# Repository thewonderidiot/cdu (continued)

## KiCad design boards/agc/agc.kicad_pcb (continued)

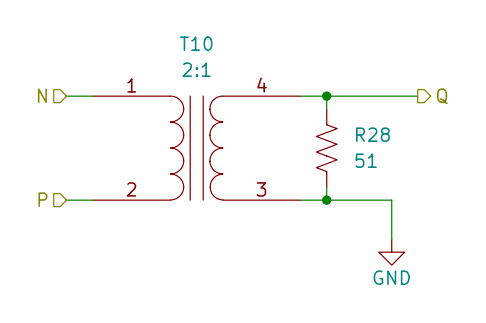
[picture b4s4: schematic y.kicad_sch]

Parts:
R28: 51; R_0603_1608Metric
T10: 2:1; Vigortronix_VTX-111

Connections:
/CDUXP: R28.1, T10.4 (SB); also elsewhere on the board
/CT+PGH: T10.1 (AA); also elsewhere on the board
/CT+PGL: T10.2 (AB); also elsewhere on the board
GND: R28.2, T10.3 (SA); also elsewhere on the board

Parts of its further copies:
R9, R10, R11, R12, R13, R24, R25, R26, R27: 51; R_0603_1608Metric
T1, T2, T3, T4, T5, T6, T7, T8, T9: 2:1; Vigortronix_VTX-111

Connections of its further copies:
/AT+PGH: T4.1 (AA); also elsewhere on the board
/AT+PGL: T4.2 (AB); also elsewhere on the board
/AT-PGH: T5.1 (AA); also elsewhere on the board
/AT-PGL: T5.2 (AB); also elsewhere on the board
/BT+PGH: T2.1 (AA); also elsewhere on the board
/BT+PGL: T2.2 (AB); also elsewhere on the board
/BT-PGH: T3.1 (AA); also elsewhere on the board
/BT-PGL: T3.2 (AB); also elsewhere on the board
/CDUXM: R9.1, T1.4 (SB); also elsewhere on the board
/CDUYM: R13.1, T5.4 (SB); also elsewhere on the board
/CDUYP: R12.1, T4.4 (SB); also elsewhere on the board
/CDUZM: R11.1, T3.4 (SB); also elsewhere on the board
/CDUZP: R10.1, T2.4 (SB); also elsewhere on the board
/CT-PGH: T1.1 (AA); also elsewhere on the board
/CT-PGL: T1.2 (AB); also elsewhere on the board
/DT+PGH: T8.1 (AA); also elsewhere on the board
/DT+PGL: T8.2 (AB); also elsewhere on the board
/DT-PGH: T9.1 (AA); also elsewhere on the board
/DT-PGL: T9.2 (AB); also elsewhere on the board
/ET+PGH: T6.1 (AA); also elsewhere on the board
/ET+PGL: T6.2 (AB); also elsewhere on the board
/ET-PGH: T7.1 (AA); also elsewhere on the board
/ET-PGL: T7.2 (AB); also elsewhere on the board
/SHAFTM: R27.1, T9.4 (SB); also elsewhere on the board
/SHAFTP: R26.1, T8.4 (SB); also elsewhere on the board
/TRNM: R25.1, T7.4 (SB); also elsewhere on the board
/TRNP: R24.1, T6.4 (SB); also elsewhere on the board
GND: R9.2, R10.2, R11.2, R12.2, R13.2, R24.2, R25.2, R26.2, R27.2, T1.3 (SA), T2.3 (SA), T3.3 (SA), T4.3 (SA), T5.3 (SA), T6.3 (SA), T7.3 (SA), T8.3 (SA), T9.3 (SA); also elsewhere on the board

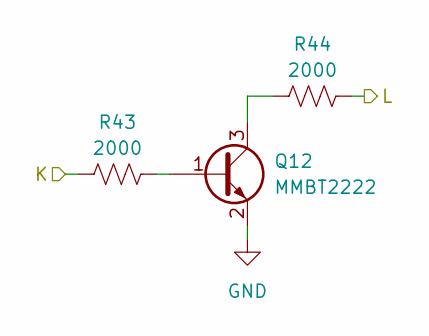
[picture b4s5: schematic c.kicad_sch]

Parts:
Q12: MMBT2222; SOT-23
R43, R44: 2000; R_0603_1608Metric

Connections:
/ISSTDC: R43.1; also elsewhere on the board
/PSATDC: R44.2; also elsewhere on the board
GND: Q12.2 (E); also elsewhere on the board
unnamed: Q12.1 (B), R43.2
unnamed: Q12.3 (C), R44.1

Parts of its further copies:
Q1, Q2, Q3, Q4, Q5, Q6, Q7: MMBT2222; SOT-23
R16, R17, R18, R19, R20, R21, R22, R23, R29, R30, R31, R32, R33, R34: 2000; R_0603_1608Metric

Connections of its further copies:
/AGCCA: R34.2; also elsewhere on the board
/AGCDAE: R21.2; also elsewhere on the board
/AGCEEC: R19.2; also elsewhere on the board
/AGCRRZ: R23.2; also elsewhere on the board
/AGCSAT: R30.2; also elsewhere on the board
/AGCTVC: R32.2; also elsewhere on the board
/AGCZ: R18.2; also elsewhere on the board
/COARSE: R33.1; also elsewhere on the board
/ENERIM: R16.1; also elsewhere on the board
/ENEROP: R20.1; also elsewhere on the board
/S4BTAK: R29.1; also elsewhere on the board
/TVCNAB: R31.1; also elsewhere on the board
/ZIMCDU: R17.1; also elsewhere on the board
/ZOPCDU: R22.1; also elsewhere on the board
GND: Q1.2 (E), Q2.2 (E), Q3.2 (E), Q4.2 (E), Q5.2 (E), Q6.2 (E), Q7.2 (E); also elsewhere on the board
unnamed: Q1.1 (B), R17.2
unnamed: Q1.3 (C), R18.1
unnamed: Q2.1 (B), R16.2
unnamed: Q2.3 (C), R19.1
unnamed: Q3.1 (B), R20.2
unnamed: Q3.3 (C), R21.1
unnamed: Q4.1 (B), R22.2
unnamed: Q4.3 (C), R23.1
unnamed: Q5.1 (B), R29.2
unnamed: Q5.3 (C), R30.1
unnamed: Q6.1 (B), R31.2
unnamed: Q6.3 (C), R32.1
unnamed: Q7.1 (B), R33.2
unnamed: Q7.3 (C), R34.1

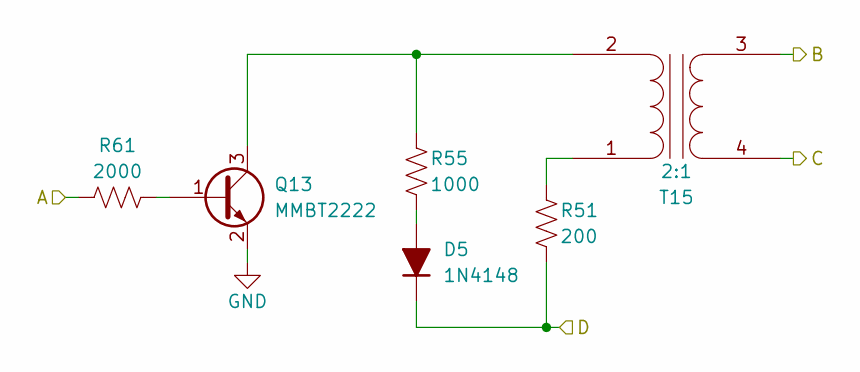
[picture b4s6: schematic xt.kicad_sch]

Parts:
D5: 1N4148; D_SOD-323
Q13: MMBT2222; SOT-23
R51: 200; R_0603_1608Metric
R55: 1000; R_0603_1608Metric
R61: 2000; R_0603_1608Metric
T15: 2:1; Vigortronix_VTX-111

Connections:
/CDUXDP: R61.1; also elsewhere on the board
/CF+PCH: T15.4 (SB); also elsewhere on the board
/CF+PCL: T15.3 (SA); also elsewhere on the board
/P1/J: D5.1 (K), R51.2; also elsewhere on the board
GND: Q13.2 (E); also elsewhere on the board
unnamed: D5.2 (A), R55.2
unnamed: Q13.1 (B), R61.2
unnamed: Q13.3 (C), R55.1, T15.2 (AB)
unnamed: R51.1, T15.1 (AA)

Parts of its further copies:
D1, D2, D3, D4, D6, D7, D8, D9, D10, D11, D12, D13, D14, D15, D16: 1N4148; D_SOD-323
Q8, Q9, Q10, Q11, Q14, Q15, Q16, Q17, Q18, Q19, Q20, Q21, Q22, Q23, Q24: MMBT2222; SOT-23
R35, R36, R37, R38, R52, R53, R54, R67, R70, R72, R74, R81, R82, R83, R84: 200; R_0603_1608Metric
R39, R40, R41, R42, R56, R57, R58, R68, R69, R71, R73, R85, R86, R87, R88: 1000; R_0603_1608Metric
R45, R46, R47, R48, R62, R63, R64, R75, R76, R77, R78, R91, R92, R93, R94: 2000; R_0603_1608Metric
T11, T12, T13, T14, T16, T17, T18, T19, T20, T21, T22, T23, T24, T25, T26: 2:1; Vigortronix_VTX-111

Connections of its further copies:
/25KPH: T22.4 (SB); also elsewhere on the board
/25KPL: T22.3 (SA); also elsewhere on the board
/25KPPS: R78.1; also elsewhere on the board
/800RH: T24.4 (SB); also elsewhere on the board
/800RL: T24.3 (SA); also elsewhere on the board
/800RST: R92.1; also elsewhere on the board
/800SET: R91.1; also elsewhere on the board
/800SH: T23.4 (SB); also elsewhere on the board
/800SL: T23.3 (SA); also elsewhere on the board
/3200A: R93.1; also elsewhere on the board
/3200AH: T25.4 (SB); also elsewhere on the board
/3200AL: T25.3 (SA); also elsewhere on the board
/3200B: R94.1; also elsewhere on the board
/3200BH: T26.4 (SB); also elsewhere on the board
/3200BL: T26.3 (SA); also elsewhere on the board
/AF+PCH: T17.4 (SB); also elsewhere on the board
/AF+PCL: T17.3 (SA); also elsewhere on the board
/AF-PCH: T18.4 (SB); also elsewhere on the board
/AF-PCL: T18.3 (SA); also elsewhere on the board
/BF+PCH: T20.4 (SB); also elsewhere on the board
/BF+PCL: T20.3 (SA); also elsewhere on the board
/BF-PCH: T21.4 (SB); also elsewhere on the board
/BF-PCL: T21.3 (SA); also elsewhere on the board
/CDUCLK: R75.1; also elsewhere on the board
/CDUXDM: R62.1; also elsewhere on the board
/CDUYDM: R64.1; also elsewhere on the board
/CDUYDP: R63.1; also elsewhere on the board
/CDUZDM: R77.1; also elsewhere on the board
/CDUZDP: R76.1; also elsewhere on the board
/CF-PCH: T16.4 (SB); also elsewhere on the board
/CF-PCL: T16.3 (SA); also elsewhere on the board
/CLOCKH: T19.4 (SB); also elsewhere on the board
/CLOCKL: T19.3 (SA); also elsewhere on the board
/DF+PCH: T13.4 (SB); also elsewhere on the board
/DF+PCL: T13.3 (SA); also elsewhere on the board
/DF-PCH: T14.4 (SB); also elsewhere on the board
/DF-PCL: T14.3 (SA); also elsewhere on the board
/EF+PCH: T11.4 (SB); also elsewhere on the board
/EF+PCL: T11.3 (SA); also elsewhere on the board
/EF-PCH: T12.4 (SB); also elsewhere on the board
/EF-PCL: T12.3 (SA); also elsewhere on the board
/P1/J: D6.1 (K), D7.1 (K), D8.1 (K), R52.2, R53.2, R54.2; also elsewhere on the board
/P2/J: D1.1 (K), D2.1 (K), D3.1 (K), D4.1 (K), R35.2, R36.2, R37.2, R38.2; also elsewhere on the board
/P3/J: D13.1 (K), D14.1 (K), D15.1 (K), D16.1 (K), R81.2, R82.2, R83.2, R84.2; also elsewhere on the board
/P4/J: D9.1 (K), D10.1 (K), D11.1 (K), D12.1 (K), R67.2, R70.2, R72.2, R74.2; also elsewhere on the board
/SHFTDM: R48.1; also elsewhere on the board
/SHFTDP: R47.1; also elsewhere on the board
/TRNDM: R46.1; also elsewhere on the board
/TRNDP: R45.1; also elsewhere on the board
GND: Q8.2 (E), Q9.2 (E), Q10.2 (E), Q11.2 (E), Q14.2 (E), Q15.2 (E), Q16.2 (E), Q17.2 (E), Q18.2 (E), Q19.2 (E), Q20.2 (E), Q21.2 (E), Q22.2 (E), Q23.2 (E), Q24.2 (E); also elsewhere on the board
unnamed: D1.2 (A), R39.2
unnamed: D2.2 (A), R40.2
unnamed: D3.2 (A), R41.2
unnamed: D4.2 (A), R42.2
unnamed: D6.2 (A), R56.2
unnamed: D7.2 (A), R57.2
unnamed: D8.2 (A), R58.2
unnamed: D9.2 (A), R68.2
unnamed: D10.2 (A), R69.2
unnamed: D11.2 (A), R71.2
unnamed: D12.2 (A), R73.2
unnamed: D13.2 (A), R85.2
unnamed: D14.2 (A), R86.2
unnamed: D15.2 (A), R87.2
unnamed: D16.2 (A), R88.2
unnamed: Q8.1 (B), R45.2
unnamed: Q8.3 (C), R39.1, T11.2 (AB)
unnamed: Q9.1 (B), R46.2
unnamed: Q9.3 (C), R40.1, T12.2 (AB)
unnamed: Q10.1 (B), R47.2
unnamed: Q10.3 (C), R41.1, T13.2 (AB)
unnamed: Q11.1 (B), R48.2
unnamed: Q11.3 (C), R42.1, T14.2 (AB)
unnamed: Q14.1 (B), R62.2
unnamed: Q14.3 (C), R56.1, T16.2 (AB)
unnamed: Q15.1 (B), R63.2
unnamed: Q15.3 (C), R57.1, T17.2 (AB)
unnamed: Q16.1 (B), R64.2
unnamed: Q16.3 (C), R58.1, T18.2 (AB)
unnamed: Q17.1 (B), R75.2
unnamed: Q17.3 (C), R68.1, T19.2 (AB)
unnamed: Q18.1 (B), R76.2
unnamed: Q18.3 (C), R69.1, T20.2 (AB)
unnamed: Q19.1 (B), R77.2
unnamed: Q19.3 (C), R71.1, T21.2 (AB)
unnamed: Q20.1 (B), R78.2
unnamed: Q20.3 (C), R73.1, T22.2 (AB)
unnamed: Q21.1 (B), R91.2
unnamed: Q21.3 (C), R85.1, T23.2 (AB)
unnamed: Q22.1 (B), R92.2
unnamed: Q22.3 (C), R86.1, T24.2 (AB)
unnamed: Q23.1 (B), R93.2
unnamed: Q23.3 (C), R87.1, T25.2 (AB)
unnamed: Q24.1 (B), R94.2
unnamed: Q24.3 (C), R88.1, T26.2 (AB)
unnamed: R35.1, T11.1 (AA)
unnamed: R36.1, T12.1 (AA)
unnamed: R37.1, T13.1 (AA)
unnamed: R38.1, T14.1 (AA)
unnamed: R52.1, T16.1 (AA)
unnamed: R53.1, T17.1 (AA)
unnamed: R54.1, T18.1 (AA)
unnamed: R67.1, T19.1 (AA)
unnamed: R70.1, T20.1 (AA)
unnamed: R72.1, T21.1 (AA)
unnamed: R74.1, T22.1 (AA)
unnamed: R81.1, T23.1 (AA)
unnamed: R82.1, T24.1 (AA)
unnamed: R83.1, T25.1 (AA)
unnamed: R84.1, T26.1 (AA)

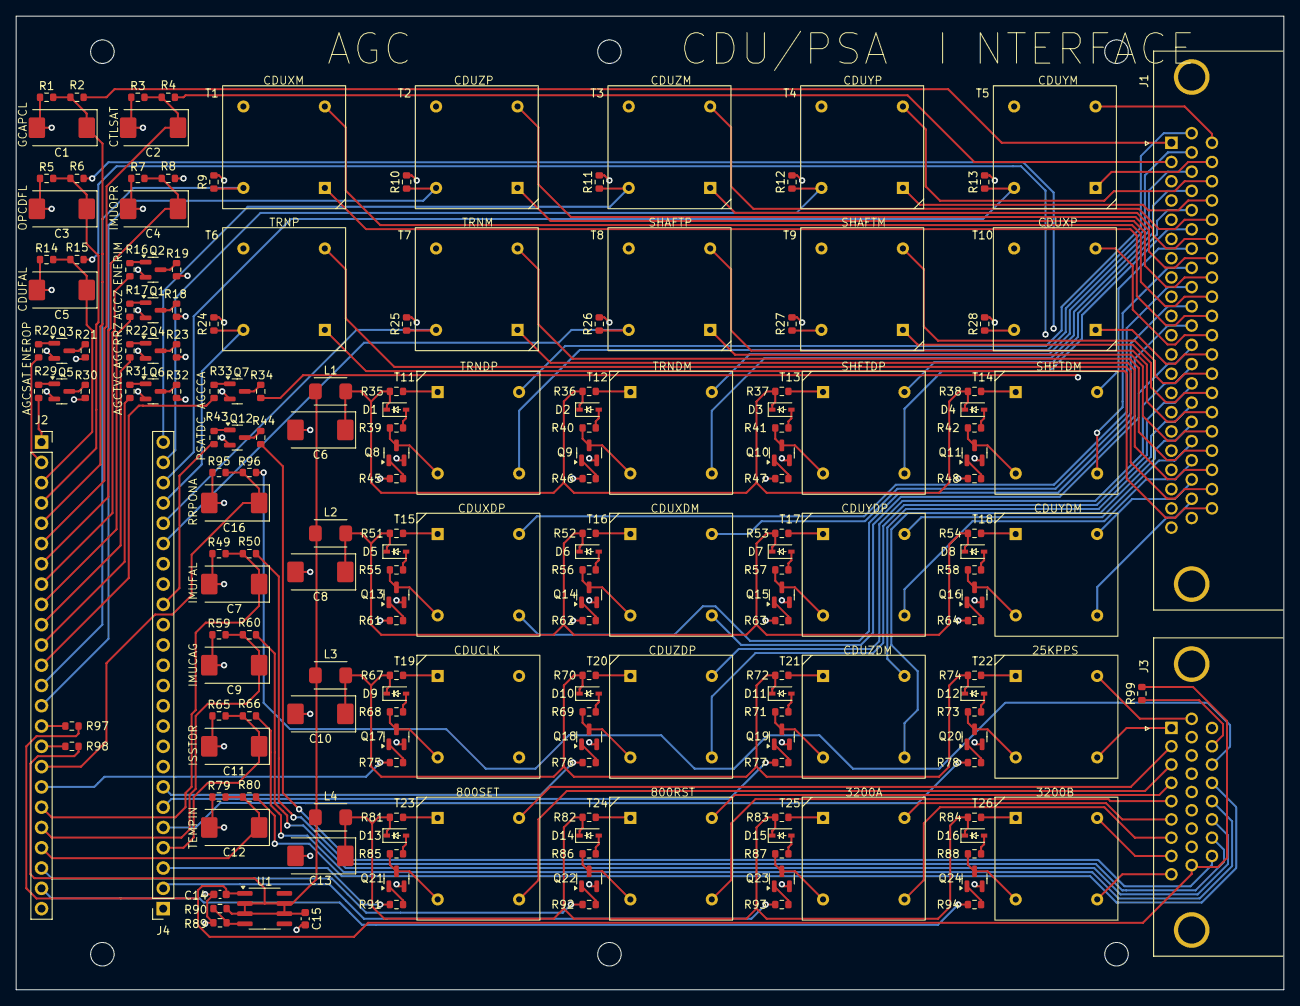
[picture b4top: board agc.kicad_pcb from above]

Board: 4 copper layers, 158.7 x 121.9 mm, 196 parts (0 on the bottom side), 205 nets.

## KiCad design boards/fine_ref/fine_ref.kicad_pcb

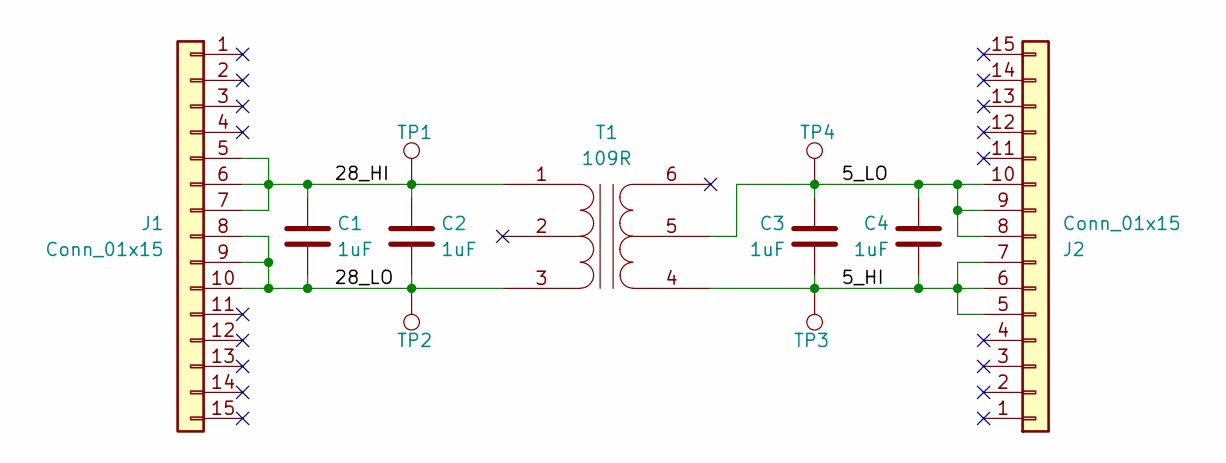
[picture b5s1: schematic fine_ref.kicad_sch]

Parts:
C1, C2, C3, C4: 1uF; C_Rect_L13.0mm_W6.0mm_P10.00mm_FKS3_FKP3_MKS4
J1, J2: Conn_01x15; PinHeader_1x15_P2.54mm_Vertical
T1: 109R; Hammond_109
TP1, TP2, TP3, TP4: TestPoint; TestPoint_Keystone_5000-5004_Miniature

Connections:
/5_HI: C3.2, C4.2, J2.5, J2.6, J2.7, T1.4 (SA), TP3.1
/5_LO: C3.1, C4.1, J2.8, J2.9, J2.10, T1.5 (SC), TP4.1
/28_HI: C1.1, C2.1, J1.5, J1.6, J1.7, T1.1 (AA), TP1.1
/28_LO: C1.2, C2.2, J1.8, J1.9, J1.10, T1.3 (AB), TP2.1

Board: 2 copper layers, 11 parts (2 on the bottom side), 4 nets, no tracks yet.

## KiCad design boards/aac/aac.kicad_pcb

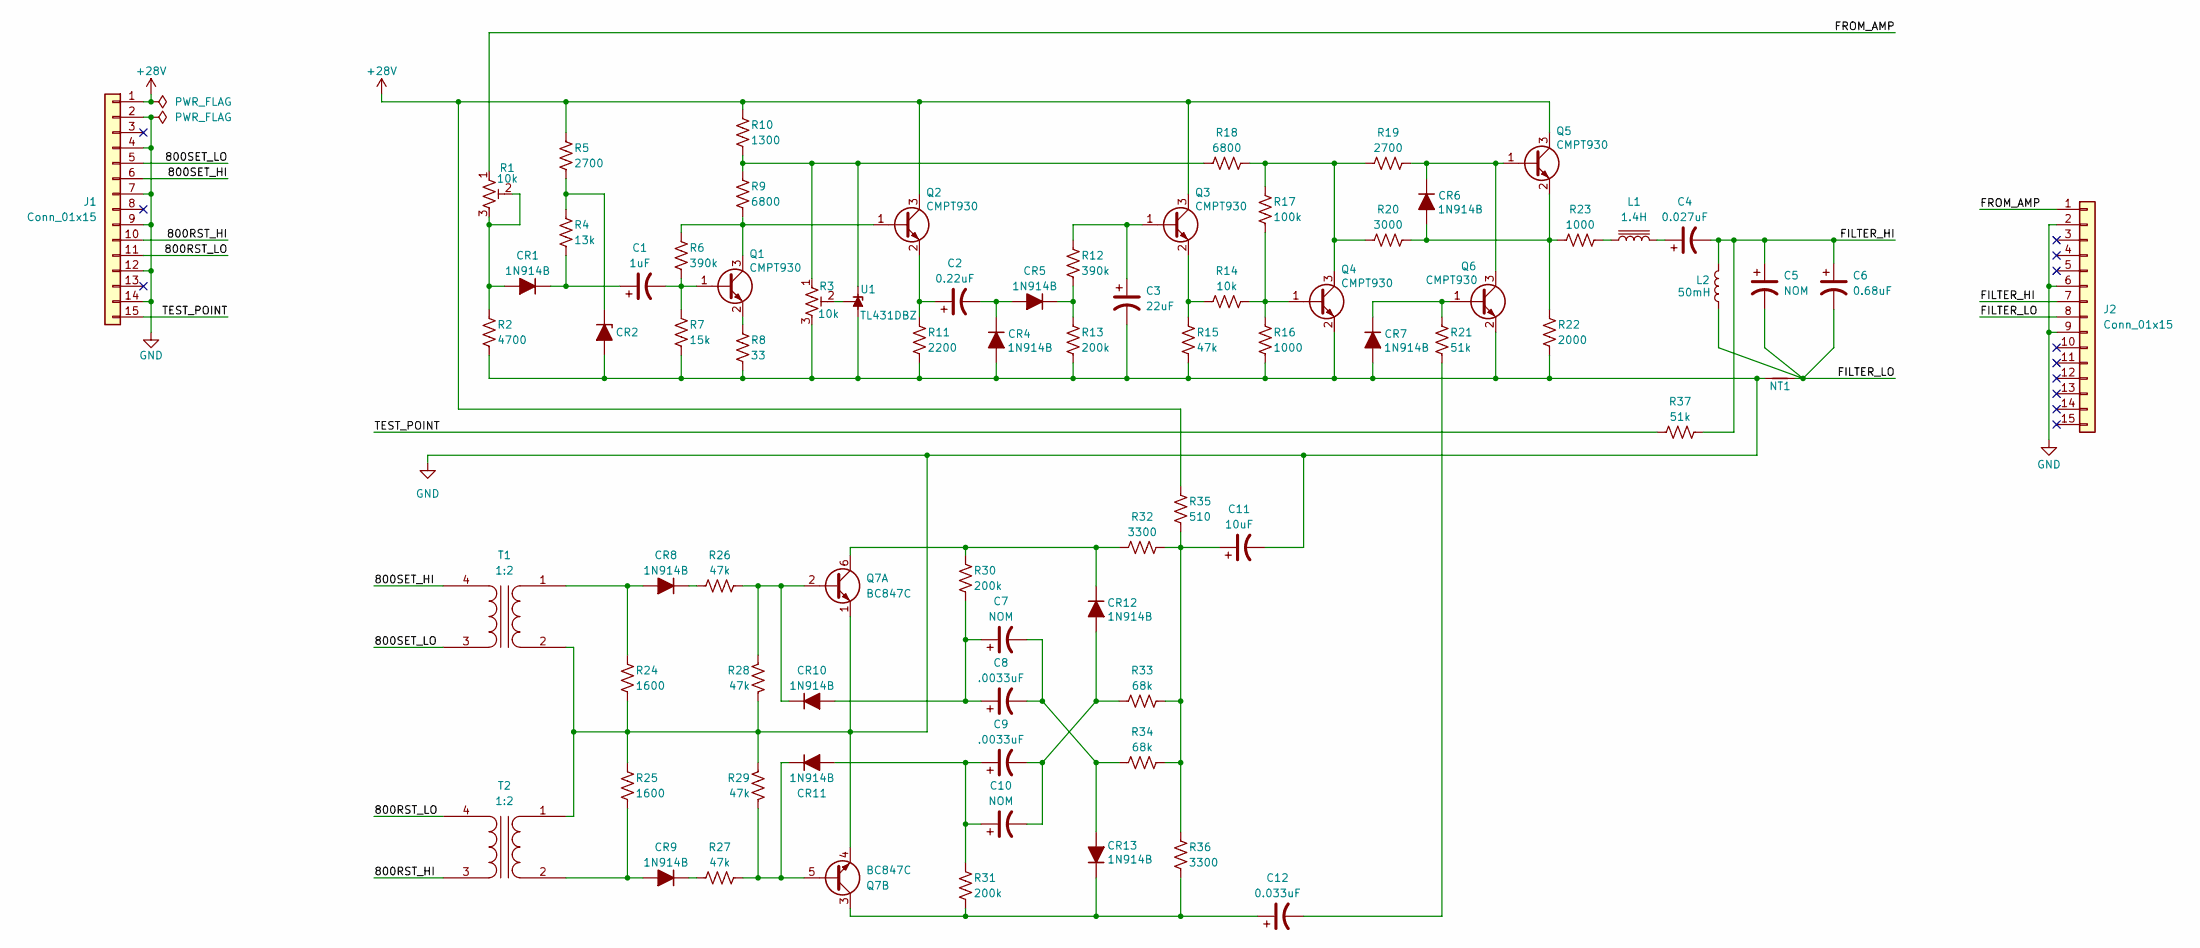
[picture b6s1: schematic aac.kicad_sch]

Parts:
C1: 1uF; CP_EIA-3216-18_Kemet-A; Rating 35V; Tolerance 10%
C2: 0.22uF; CP_EIA-3216-18_Kemet-A; Rating 35V; Tolerance 10%
C3: 22uF; CP_EIA-7343-31_Kemet-D; Rating 35V; Tolerance 10%
C4: 0.027uF; C_Rect_L7.2mm_W2.5mm_P5.00mm_FKS2_FKP2_MKS2_MKP2; Rating 50V; Tolerance 10%; MPN B32529C0273J289
C5, C7, C10: NOM; C_Rect_L7.2mm_W2.5mm_P5.00mm_FKS2_FKP2_MKS2_MKP2; Rating 200V; Tolerance 5%
C6: 0.68uF; C_Rect_L7.2mm_W4.5mm_P5.00mm_FKS2_FKP2_MKS2_MKP2; Rating 200V; Tolerance 5%
C8, C9: .0033uF; C_Rect_L7.2mm_W2.5mm_P5.00mm_FKS2_FKP2_MKS2_MKP2; Rating 200V; Tolerance 5%
C11: 10uF; CP_EIA-7343-31_Kemet-D; Rating 35V; Tolerance 10%
C12: 0.033uF; C_Rect_L7.2mm_W2.5mm_P5.00mm_FKS2_FKP2_MKS2_MKP2; Rating 50V; Tolerance 10%
CR1, CR4, CR5, CR6, CR7, CR8, CR9, CR10, CR11, CR12, CR13: 1N914B; D_SOD-323
CR2: 17V; D_SOD-123
J1, J2: Conn_01x15; PinHeader_1x15_P2.54mm_Vertical
L1: 1.4H; SPT-179
L2: 50mH; L_Radial_D8.7mm_P5.00mm_Fastron_07HCP
NT1: NetTie_2; NetTie-2_SMD_Pad0.5mm
Q1, Q2, Q3, Q4, Q5, Q6: CMPT930; SOT-23
Q7: BC847C; SOT-363_SC-70-6
R1, R3: 10k; Potentiometer_Bourns_3296Y_Vertical
R2: 4700; R_0603_1608Metric; Rating 1/8W; Tolerance 1%
R4: 13k; R_0603_1608Metric; Rating 1/8W; Tolerance 1%
R5, R19: 2700; R_0603_1608Metric; Rating 1/4W; Tolerance 2%
R6, R12: 390k; R_0603_1608Metric; Rating 1/8W; Tolerance 5%
R7: 15k; R_0603_1608Metric; Rating 1/4W; Tolerance 2%
R8: 33; R_0603_1608Metric; Rating 1/8W; Tolerance 5%
R9, R18: 6800; R_0603_1608Metric; Rating 1/4W; Tolerance 2%
R10: 1300; R_0603_1608Metric; Rating 1/2W; Tolerance 2%
R11: 2200; R_0603_1608Metric; Rating 1/4W; Tolerance 2%
R13: 200k; R_0603_1608Metric; Rating 1/8W; Tolerance 5%
R14: 10k; R_0603_1608Metric; Rating 1/4W; Tolerance 2%
R15, R26, R27, R28, R29: 47k; R_0603_1608Metric; Rating 1/4W; Tolerance 2%
R16, R23: 1000; R_0603_1608Metric; Rating 1/4W; Tolerance 2%
R17: 100k; R_0603_1608Metric; Rating 1/4W; Tolerance 2%
R20: 3000; R_0603_1608Metric; Rating 1/4W; Tolerance 2%
R21, R37: 51k; R_0603_1608Metric; Rating 1/4W; Tolerance 2%
R22: 2000; R_0603_1608Metric; Rating 1/4W; Tolerance 2%
R24, R25: 1600; R_0603_1608Metric; Rating 1/4W; Tolerance 2%
R30, R31: 200k; R_0603_1608Metric; Rating 1/8W; Tolerance 1%
R32, R36: 3300; R_0603_1608Metric; Rating 1W; Tolerance 1%
R33, R34: 68k; R_0603_1608Metric; Rating 1/4W; Tolerance 2%
R35: 510; R_0603_1608Metric; Rating 1/2W; Tolerance 2%
T1, T2: 1:2; Vigortronix_VTX-111
U1: TL431DBZ; SOT-23

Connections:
+28V: J1.1, Q2.3 (C), Q3.3 (C), Q5.3 (C), R5.1, R10.1, R35.1
/800RST_HI: J1.10, T2.3 (SA)
/800RST_LO: J1.11, T2.4 (SB)
/800SET_HI: J1.6, T1.4 (SB)
/800SET_LO: J1.5, T1.3 (SA)
/FILTER_HI: C4.2, C5.1, C6.1, J2.7, L2.2, R37.1
/FILTER_LO: C5.2, C6.2, J2.8, L2.1, NT1.2
/FROM_AMP: J2.1, R1.1
/TEST_POINT: J1.15, R37.2
GND: C3.2, C11.2, CR2.2 (A), CR4.2 (A), CR7.2 (A), J1.2, J1.4, J1.7, J1.9, J1.12, J1.14, J2.2, J2.6, J2.9, NT1.1, Q4.2 (E), Q6.2 (E), Q7.1 (E1), Q7.4 (E2), R2.2, R3.3, R7.2, R8.2, R11.2, R13.2, R15.2, R16.2, R22.2, R24.2, R25.1, R28.2, R29.1, T1.2 (AB), T2.1 (AA), U1.3 (A)
unnamed: C4.1, L1.12
unnamed: C11.1, R32.1, R33.1, R34.1, R35.2, R36.1
unnamed: C12.2, R21.2
unnamed: CR1.2 (A), R1.2, R1.3, R2.1
unnamed: C1.1, CR1.1 (K), R4.2
unnamed: CR2.1 (K), R4.1, R5.2
unnamed: C2.2, CR4.1 (K), CR5.2 (A)
unnamed: CR5.1 (K), R12.2, R13.1
unnamed: CR6.2 (A), Q5.2 (E), R20.1, R22.1, R23.2
unnamed: CR6.1 (K), Q5.1 (B), Q6.3 (C), R19.1
unnamed: CR7.1 (K), Q6.1 (B), R21.1
unnamed: CR8.2 (A), R24.1, T1.1 (AA)
unnamed: CR8.1 (K), R26.2
unnamed: CR9.2 (A), R25.2, T2.2 (AB)
unnamed: CR9.1 (K), R27.2
unnamed: C7.1, C8.1, CR10.2 (A), R30.2
unnamed: CR10.1 (K), Q7.2 (B1), R26.1, R28.1
unnamed: C9.1, C10.1, CR11.2 (A), R31.1
unnamed: CR11.1 (K), Q7.5 (B2), R27.1, R29.2
unnamed: C9.2, C10.2, CR12.2 (A), R33.2
unnamed: CR12.1 (K), Q7.6 (C1), R30.1, R32.2
unnamed: C7.2, C8.2, CR13.2 (A), R34.2
unnamed: C12.1, CR13.1 (K), Q7.3 (C2), R31.2, R36.2
unnamed: L1.1, R23.1
unnamed: C1.2, Q1.1 (B), R6.2, R7.1
unnamed: Q1.3 (C), Q2.1 (B), R6.1, R9.2
unnamed: Q1.2 (E), R8.1
unnamed: C2.1, Q2.2 (E), R11.1
unnamed: C3.1, Q3.1 (B), R12.1
unnamed: Q3.2 (E), R14.2, R15.1
unnamed: Q4.1 (B), R14.1, R16.1, R17.2
unnamed: Q4.3 (C), R17.1, R18.1, R19.2, R20.2
unnamed: R3.1, R9.1, R10.2, R18.2, U1.1 (K)
unnamed: R3.2, U1.2 (REF)

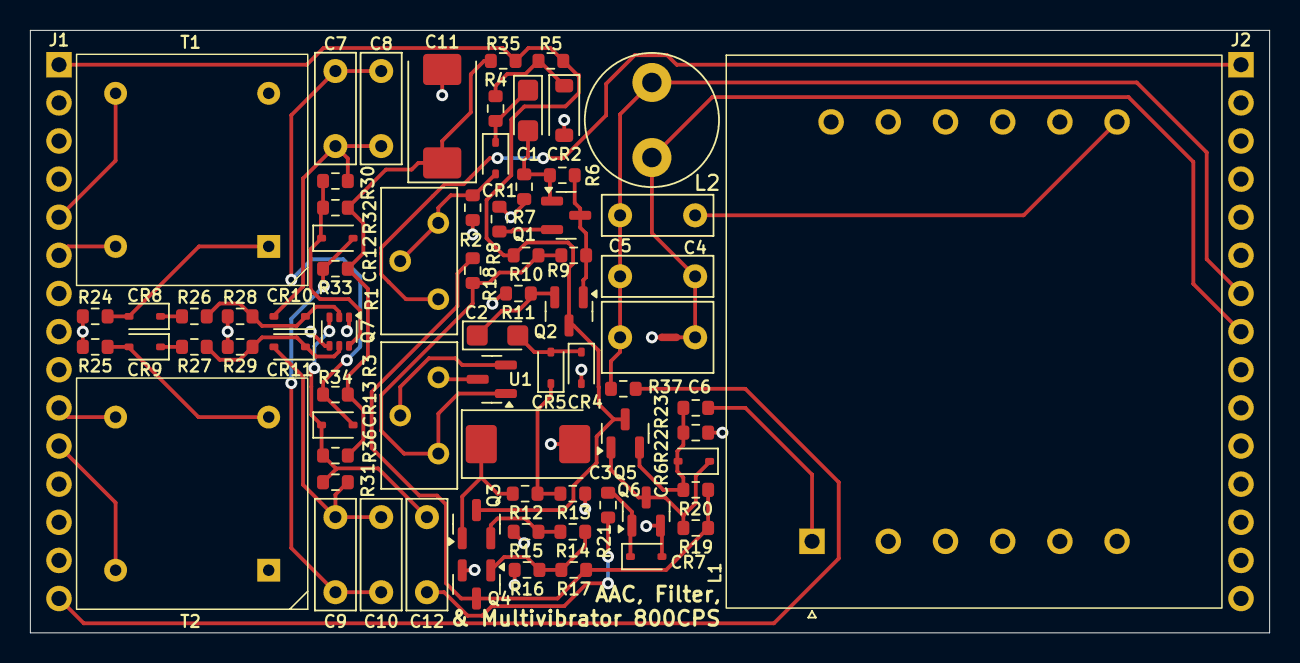
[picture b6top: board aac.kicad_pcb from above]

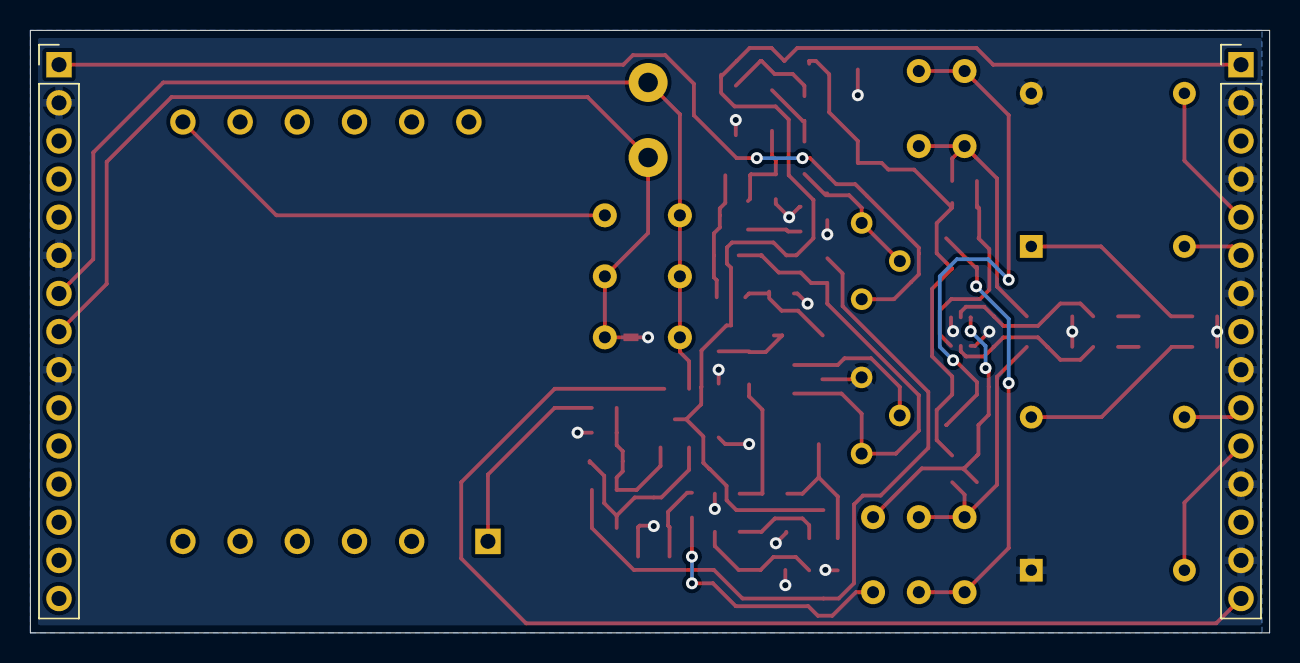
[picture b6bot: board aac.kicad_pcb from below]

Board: 2 copper layers, 82.5 x 40.1 mm, 76 parts (2 on the bottom side), 44 nets.

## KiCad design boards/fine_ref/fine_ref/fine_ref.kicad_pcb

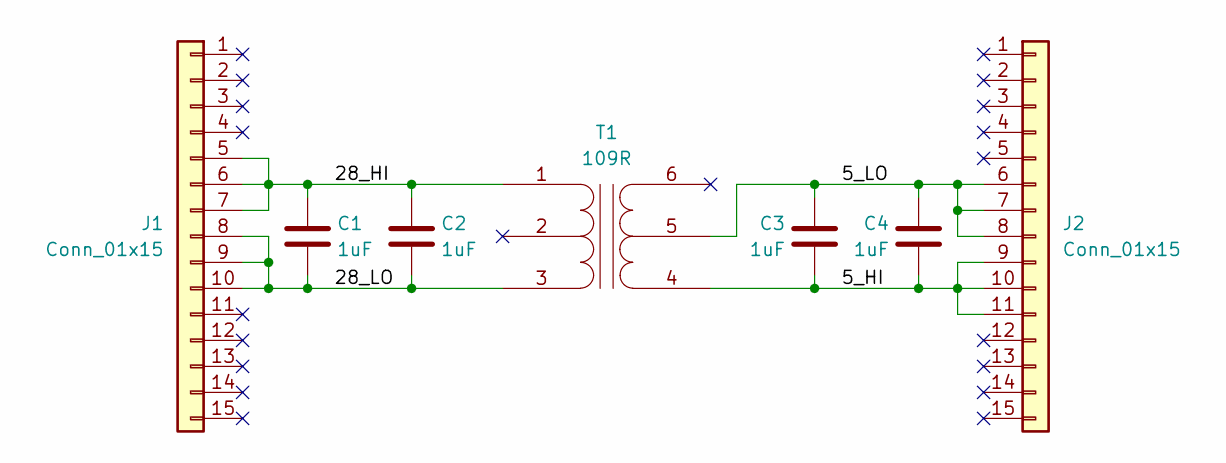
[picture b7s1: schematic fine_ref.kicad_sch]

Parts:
C1, C2, C3, C4: 1uF; C_Rect_L13.0mm_W6.0mm_P10.00mm_FKS3_FKP3_MKS4
J1, J2: Conn_01x15; PinHeader_1x15_P2.54mm_Vertical
T1: 109R; Hammond_109

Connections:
/5_HI: C3.2, C4.2, J2.9, J2.10, J2.11, T1.4 (SA)
/5_LO: C3.1, C4.1, J2.6, J2.7, J2.8, T1.5 (SC)
/28_HI: C1.1, C2.1, J1.5, J1.6, J1.7, T1.1 (AA)
/28_LO: C1.2, C2.2, J1.8, J1.9, J1.10, T1.3 (AB)

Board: 2 copper layers, 7 parts (2 on the bottom side), 4 nets, no tracks yet.

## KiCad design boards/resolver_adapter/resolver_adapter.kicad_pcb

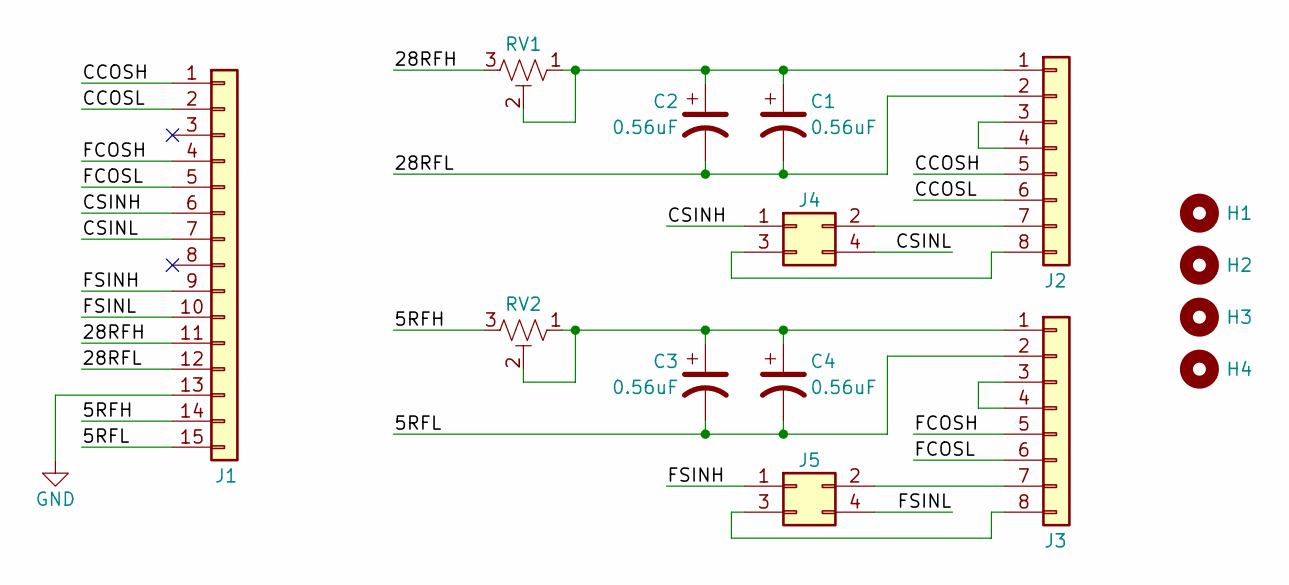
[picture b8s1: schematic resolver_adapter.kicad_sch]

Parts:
C1, C2, C3, C4: 0.56uF; C_Rect_L18.0mm_W5.0mm_P15.00mm_O0.6mm_FKS3_FKP3
H1, H2, H3, H4: MountingHole; MountingHole_4-40
J1: Conn_01x15; DSUB-15-HD_Female_Horizontal_P2.29x1.98mm_EdgePinOffset3.03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
J2, J3: Conn_01x08; DF11-8DP-2DS
J4, J5: Conn_02x02_Odd_Even; PinHeader_2x02_P2.00mm_Vertical
RV1, RV2: R_Potentiometer_Trim_US; Potentiometer_Bourns_3296Y_Vertical

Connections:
/5RFH: J1.14, RV2.3
/5RFL: C3.2, C4.2, J1.15, J3.2
/28RFH: J1.11, RV1.3
/28RFL: C1.2, C2.2, J1.12, J2.2
/CCOSH: J1.1, J2.5
/CCOSL: J1.2, J2.6
/CSINH: J1.6, J4.1
/CSINL: J1.7, J4.4
/FCOSH: J1.4, J3.5
/FCOSL: J1.5, J3.6
/FSINH: J1.9, J5.1
/FSINL: J1.10, J5.4
GND: J1.13
unnamed: C1.1, C2.1, J2.1, RV1.1, RV1.2
unnamed: J2.3, J2.4
unnamed: J2.7, J4.2
unnamed: J2.8, J4.3
unnamed: C3.1, C4.1, J3.1, RV2.1, RV2.2
unnamed: J3.3, J3.4
unnamed: J3.7, J5.2
unnamed: J3.8, J5.3

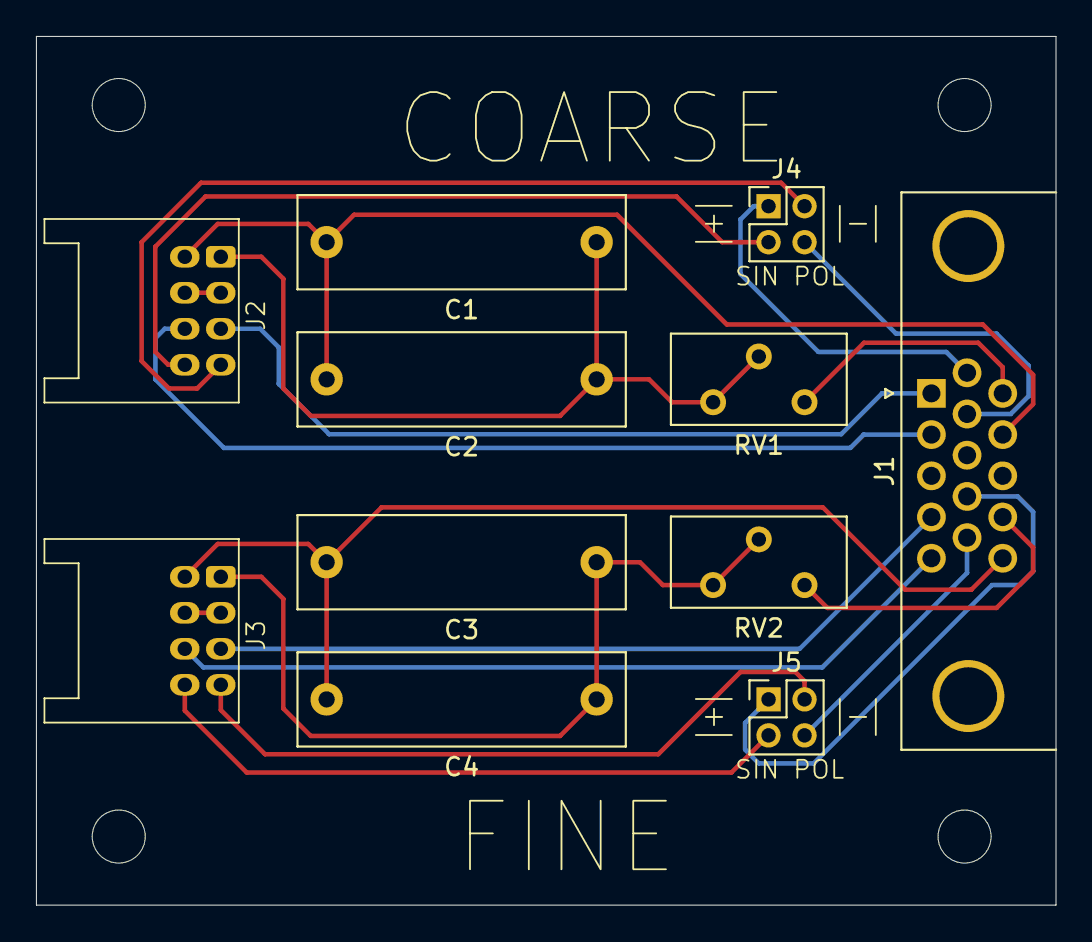
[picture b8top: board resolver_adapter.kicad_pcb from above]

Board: 2 copper layers, 56.6 x 48.3 mm, 15 parts (0 on the bottom side), 20 nets.

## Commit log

2020-03-13 Added initial CDU simulator. Much more NOR logic work is needed.
2020-03-13 Digital mode: corrected old differences from 2010095 and began added new gates
2020-03-13 Digital mode: added more gates, up through production of 800LHI
2020-03-13 Coarse: added ambiguity detect and corrected coarse and EC&L module numbers
2020-03-13 Digital mode: added ambiguity detect logic for inner gimbal (channel A)
2020-03-13 Added moding circuitry to Mode and Digital Mode modules
2020-03-14 Added some gates to EC&L, and added in/broke out a bunch of test points
2020-03-14 Added an initial GTKWave save file
2020-03-14 Filled out more EC&L logic
2020-03-14 Integrated the read counter and fixed a handful of sign errors. Coarse system appears to be mostly working.
2020-03-14 Put in a temporary fix for an unknown sign error, and added an ATCA reference
2020-03-15 Corrected coarse system math (summing amplifier is inverting)
2020-03-15 Implemented beginings of fine system, as well as a simple D/A converter module to handle pulses to the AGC
2020-03-16 Added most of the fine system, which appears to be working. The CDU now appears to be able to reliably determine angles to within 0.01 degrees.
2020-03-17 Fiddling with simulation
2020-03-21 adding spice modules
2020-03-21 added summing amp
2020-03-23 Added a reassembled PDF of the 2007222 procurement spec
2020-03-23 Added a PS for the coarse module
2020-03-23 Added a PS for the D/A module
2020-03-23 Added a PS for the MSA&QR module
2020-03-23 Added an unfortunately very incomplete PS for the quadrant selector module
2020-03-23 Added an unfortunately somewhat incomplete PS for the mode module
2020-03-25 Added a stitched-together 2015566, the IMU/RR 2-wire mechanization drawing
2021-09-06 Committing old uncommitted work (will need to be reviewed)
2023-11-18 Initial steps towards synthesizable CDU logic
2023-11-25 Sim: significantly improved initial conditions
2023-11-26 Sim: tweaks necessary for compatibility with verilator
2023-12-01 Added schmitt trigger model and as-measured off/on thresholds
2023-12-01 Initial target for web CDU
2023-12-02 Added a bunch of stitched drawings
2023-12-03 Corrected error amplifier gain and saturation characteristics and fixed inversion in quadrant selector
2023-12-03 Corrected gain of ladder amplifier
2024-03-11 Reviewed and completed the digital logic modules
2024-08-01 Initial connector board
2024-08-06 Sim: add missing _CDUZ connection to EC&L
2024-08-06 Connector board: swap PSA connector for 44-pin, separate resolver and CDU references, and add some more power pins
2024-08-06 Add resolver adapter board
2025-04-20 Add AGC and AAC boards
2025-04-20 Add fine reference and compensation board
2025-05-28 Add PSA switching modules and rework fine ref
2025-06-16 Revised AGC board to include RRPONA, RD874, and 28V/14V analog sensing
2025-06-16 Corrected switch layouts for auxiliary relays and LM switching boards
2025-06-16 Add PSA backplane board
2025-08-17 Correct some quadrant selector gains
2025-08-23 Replace most gain calculations with magic numbers (sorry), increase schmitt trigger fidelity, and correct ambiguity detect thresholds
